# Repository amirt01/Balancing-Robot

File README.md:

# Balancing-Robot
This is a personal project where I am designing, building, and programming a robot that can balance on two wheels. Some goals I have for this robot are:
1. Simple Balance - if the robot is pushed, correct the disturbance and regain balance
2. Position Lock - once the robot regains its balance, return to the original location
3. Joystick Control - be able to control the robot's movement using a joystick via a phone app

I learned about stepper motors and stepper motor control, Complementary Filters, and complex PID control during this project.
## Libraries
[Arduino_LSM6DS3](https://reference.arduino.cc/reference/en/libraries/arduino_lsm6ds3/)

[WiFiNINA](https://www.arduino.cc/reference/en/libraries/wifinina/)

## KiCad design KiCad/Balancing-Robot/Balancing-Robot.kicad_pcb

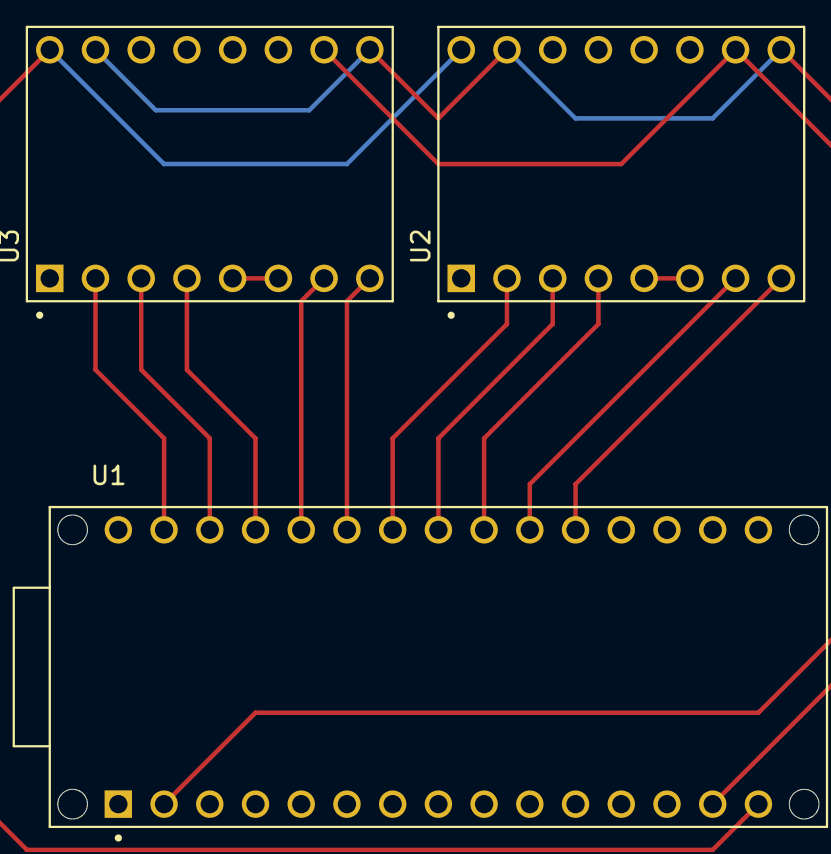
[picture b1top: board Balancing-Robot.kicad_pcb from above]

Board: 2 copper layers, 3 parts (0 on the bottom side), 15 nets.

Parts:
U1: ABX00053; MODULE_ABX00053
U2, U3: A4988_STEPPER_MOTOR_DRIVER_CARRIER; MODULE_A4988_STEPPER_MOTOR_DRIVER_CARRIER

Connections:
/D2: U1.20 (D2/GPIO25), U2.8 (DIR)
/D3: U1.21 (D3/GPIO15), U2.7 (STEP)
/D4: U1.22 (D4/GPIO26), U2.4 (MS3)
/D5: U1.23 (D5/GPIO17), U2.3 (MS2)
/D6: U1.24 (D6/GPIO18), U2.2 (MS1)
/D7: U1.25 (D7/GPIO19), U3.8 (DIR)
/D8: U1.26 (D8/GPIO20), U3.7 (STEP)
/D9: U1.27 (D9/GPIO21), U3.4 (MS3)
/D10: U1.28 (D10/GPIO5), U3.3 (MS2)
/D11: U1.29 (D11/GPIO7/COPI), U3.2 (MS1)
GND: U1.14 (GND), U1.19 (GND), U2.9 (GND), U2.15 (GND), U3.9 (GND), U3.15 (GND)
unnamed: U2.5 (~RESET), U2.6 (~SLEEP)
unnamed: U3.5 (~RESET), U3.6 (~SLEEP)
VCC: U1.15 (VIN), U2.16 (VMOT), U3.16 (VMOT)
VDD: U1.2 (+3V3), U2.10 (VDD), U3.10 (VDD)

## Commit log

2023-06-29 CAD Initial Commit
2023-06-29 Initial Code Commit
2023-06-30 uncoupled speed control using class
2023-07-01 working IMU control
2023-07-01 cleanup
2023-07-01 marginally stable balancing
2023-07-01 commenting and refactoring
2023-07-01 PID tuning
2023-07-05 circuit
2023-07-07 circuit board updates
2023-07-31 revert to different strategy
2023-08-02 working project
